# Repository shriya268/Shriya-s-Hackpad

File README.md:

# Shriya-s-Macropad
A macropad specifically designed for Roblox. The keys are necessary to play Roblox, and having only the necessary keys optimizes gaming performance. This is a macropad, not a HackPad, as I didn't use the tutorials for it and did it on my own. I made this project as a newcomer to PCB designing to learn. I've always found how daily systems such as keyboards work, but this is the first time I've made something like this myself.

# BOM

| Source     | Item                            | Quantity | Price  | Notes                                 | Link |
|------------|----------------------------------|----------|--------|----------------------------------------|------|
| AliExpress | M2 4mm Spacers                  | 5x       | $1.04  |                                        | [M2 4mm Spacers](https://www.aliexpress.us/item/3256807017784754.html?spm=a2g0o.productlist.0.0.722e6363EuH04s&mp=1&pdp_npi=5%40dis%21USD%21USD%201.48%21USD%201.04%21%21USD%201.04%21%21%21%402103277f17512608094343308ecd9e%2112000039794516573%21ct%21US%216408478558%21%211%210&_gl=1*11foqlg*_gcl_aw*R0NMLjE3NTExNDI5MTYuQ2owS0NRandwZjdDQmhDZkFSSXNBTklFVFZvTHNXX3MtcWgtVXdMc2JLR2MtUXRsWHN3RE9hdmVOSWRsZjQ3LWZ3UW1fUm92SXdEVWRtY2FBbm5ERUFMd193Y0I.*_gcl_au*MTQzODE4NjUwLjE3NTExNDI5MTY.*_ga*MTU5OTE5MTQzOC4xNzUxMjU5OTE5*_ga_VED1YSGNC7*czE3NTEyNTk5MTgkbzEkZzEkdDE3NTEyNjA4MTYkajMxJGwwJGgw&gatewayAdapt=glo2usa) |
| AliExpress | M2 7mm Spacers                  | 30x      | $2.10  |                                        | [M2 7mm Spacers](https://www.aliexpress.us/item/3256805863280885.html?spm=a2g0o.detail.0.0.1204wn00wn00uf&mp=1&pdp_npi=5%40dis%21USD%21USD%202.22%21USD%202.22%21%21USD%202.22%21%21%21%402103244817513077203134174eb19b%2112000035491390235%21ct%21US%216408478558%21%211%210&_gl=1*f6trlo*_gcl_aw*R0NMLjE3NTExNDI5MTYuQ2owS0NRandwZjdDQmhDZkFSSXNBTklFVFZvTHNXX3MtcWgtVXdMc2JLR2MtUXRsWHN3RE9hdmVOSWRsZjQ3LWZ3UW1fUm92SXdEVWRtY2FBbm5ERUFMd193Y0I.*_gcl_au*MTQzODE4NjUwLjE3NTExNDI5MTY.*_ga*MTU5OTE5MTQzOC4xNzUxMjU5OTE5*_ga_VED1YSGNC7*czE3NTEzMDc3MjAkbzIkZzAkdDE3NTEzMDc3MjAkajYwJGwwJGgw&gatewayAdapt=glo2usa) |
| AliExpress | M2 Screw Set                    | –        | $5.62  | Has all necessary lengths              | [M2 Screw Set](https://www.aliexpress.us/item/3256806973435795.html?spm=a2g0o.cart.0.0.56ac38daVxnwKY&mp=1&pdp_npi=5%40dis%21USD%21USD%205.88%21USD%205.62%21%21USD%205.62%21%21%21%402101ec1a17513583533687501ec24a%2112000039655872513%21ct%21US%216408478558%21%211%210&_gl=1*1bt5m9l*_gcl_aw*R0NMLjE3NTExNDI5MTYuQ2owS0NRandwZjdDQmhDZkFSSXNBTklFVFZvTHNXX3MtcWgtVXdMc2JLR2MtUXRsWHN3RE9hdmVOSWRsZjQ3LWZ3UW1fUm92SXdEVWRtY2FBbm5ERUFMd193Y0I.*_gcl_au*MTQzODE4NjUwLjE3NTExNDI5MTY.*_ga*MTU5OTE5MTQzOC4xNzUxMjU5OTE5*_ga_VED1YSGNC7*czE3NTEzNTc4ODYkbzQkZzEkdDE3NTEzNTgzNTQkajUyJGwwJGgw&gatewayAdapt=glo2usa)|
| AliExpress | DO-35 Diodes                    | 100x     | $0.99  |                                        | [DO-35 Diodes](https://www.aliexpress.com/item/2251832667767786.html?spm=a2g0o.cart.0.0.798a38daLnZwjx&mp=1&pdp_npi=5%40dis%21USD%21USD%203.51%21USD%203.51%21%21USD%203.51%21%21%21%40210337bc17513078928717653e059c%2167121545639%21ct%21US%216408478558%21%211%210&_gl=1*huzjkp*_gcl_aw*R0NMLjE3NTExNDI5MTYuQ2owS0NRandwZjdDQmhDZkFSSXNBTklFVFZvTHNXX3MtcWgtVXdMc2JLR2MtUXRsWHN3RE9hdmVOSWRsZjQ3LWZ3UW1fUm92SXdEVWRtY2FBbm5ERUFMd193Y0I.*_gcl_au*MTQzODE4NjUwLjE3NTExNDI5MTY.*_ga*MTU5OTE5MTQzOC4xNzUxMjU5OTE5*_ga_VED1YSGNC7*czE3NTEzMDc3MjAkbzIkZzEkdDE3NTEzMDc5MTQkajMkbDAkaDA) |
| AliExpress | Cherry MX Keycaps               | 104x     | $5.01  |                                        | [Cherry MX Keycaps](https://www.aliexpress.us/item/3256808108935624.html?spm=a2g0o.cart.0.0.3f1638daol5bNF&mp=1&pdp_npi=5%40dis%21USD%21USD%205.01%21USD%205.01%21%21USD%205.01%21%21%21%40210318c317513586402145101e623c%2112000044523183107%21ct%21US%216408478558%21%211%210&_gl=1*bvs7nr*_gcl_aw*R0NMLjE3NTExNDI5MTYuQ2owS0NRandwZjdDQmhDZkFSSXNBTklFVFZvTHNXX3MtcWgtVXdMc2JLR2MtUXRsWHN3RE9hdmVOSWRsZjQ3LWZ3UW1fUm92SXdEVWRtY2FBbm5ERUFMd193Y0I.*_gcl_au*MTQzODE4NjUwLjE3NTExNDI5MTY.*_ga*MTU5OTE5MTQzOC4xNzUxMjU5OTE5*_ga_VED1YSGNC7*czE3NTEzNTc4ODYkbzQkZzEkdDE3NTEzNTg2MzQkajU2JGwwJGgw&gatewayAdapt=glo2usa) |
| Amazon     | Cherry MX Red Keyswitches       | 23x      | $9.60  | 20% off discount + Amazon Prime        | [Cherry MX Red Keyswitches](https://www.amazon.com/gp/product/B0CBS4HJJR/ref=ox_sc_saved_image_1?smid=AK7PAPV76H5NA&th=1) |
| Keebio     | Arduino Pro Micro               | 1x       | $7.99  | 5V 16MHz ATmega32U4                    | [Arduino Pro Micro](https://keeb.io/products/pro-micro-5v-16mhz-arduino-compatible-atmega32u4?srsltid=AfmBOoohKZiYkrMl3YAv38JQXlnb-arPQS6xtnZeeLZ4_bFDnoDUEZKH) |
| JLCPCB     | Custom PCBs                     | 5x       | $5.30  |                                        | [JLCPCB Cart](https://cart.jlcpcb.com/shopcart/cart/) |
| **Total**  |                                  |          | **$37.65** |                                      |      |

*AliExpress products are so cheap because of the welcome deal and additional coupons/discounts

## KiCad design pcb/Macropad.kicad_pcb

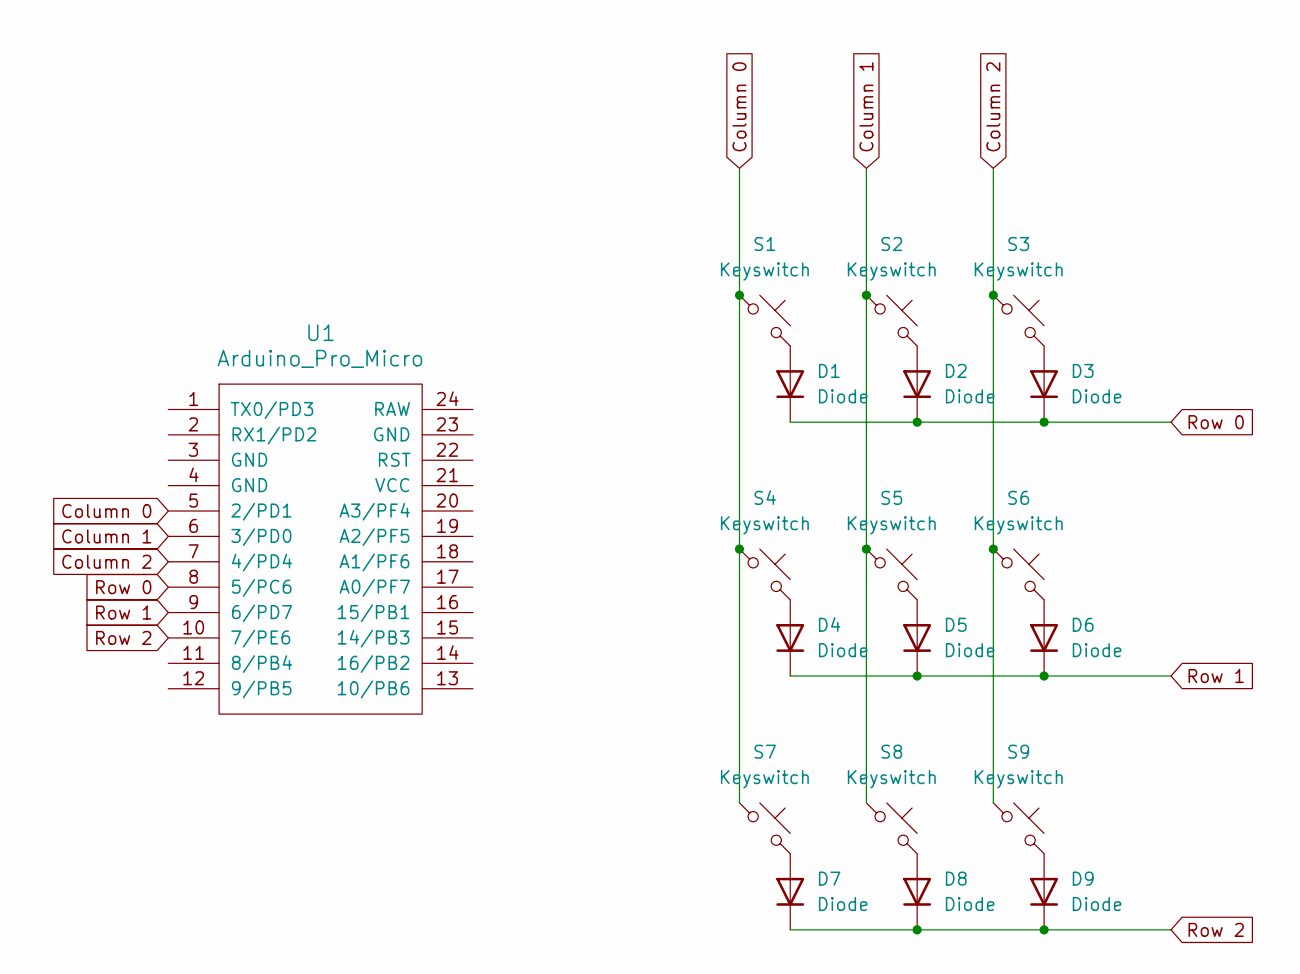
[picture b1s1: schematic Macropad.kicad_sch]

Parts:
D1, D2, D3, D4, D5, D6, D7, D8, D9: Diode; Diode_DO-35
S1, S2, S3, S4, S5, S6, S7, S8, S9: Keyswitch; MX_PCB_1.00u
U1: Arduino_Pro_Micro

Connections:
Column 0: S1.1, S4.1, S7.1, U1.5 (2/PD1)
Column 1: S2.1, S5.1, S8.1, U1.6 (3/PD0)
Column 2: S3.1, S6.1, S9.1, U1.7 (4/PD4)
unnamed: D1.2 (A), S1.2
unnamed: D2.2 (A), S2.2
unnamed: D3.2 (A), S3.2
unnamed: D4.2 (A), S4.2
unnamed: D5.2 (A), S5.2
unnamed: D6.2 (A), S6.2
unnamed: D7.2 (A), S7.2
unnamed: D8.2 (A), S8.2
unnamed: D9.2 (A), S9.2
Row 0: D1.1 (K), D2.1 (K), D3.1 (K), U1.8 (5/PC6)
Row 1: D4.1 (K), D5.1 (K), D6.1 (K), U1.9 (6/PD7)
Row 2: D7.1 (K), D8.1 (K), D9.1 (K), U1.10 (7/PE6)

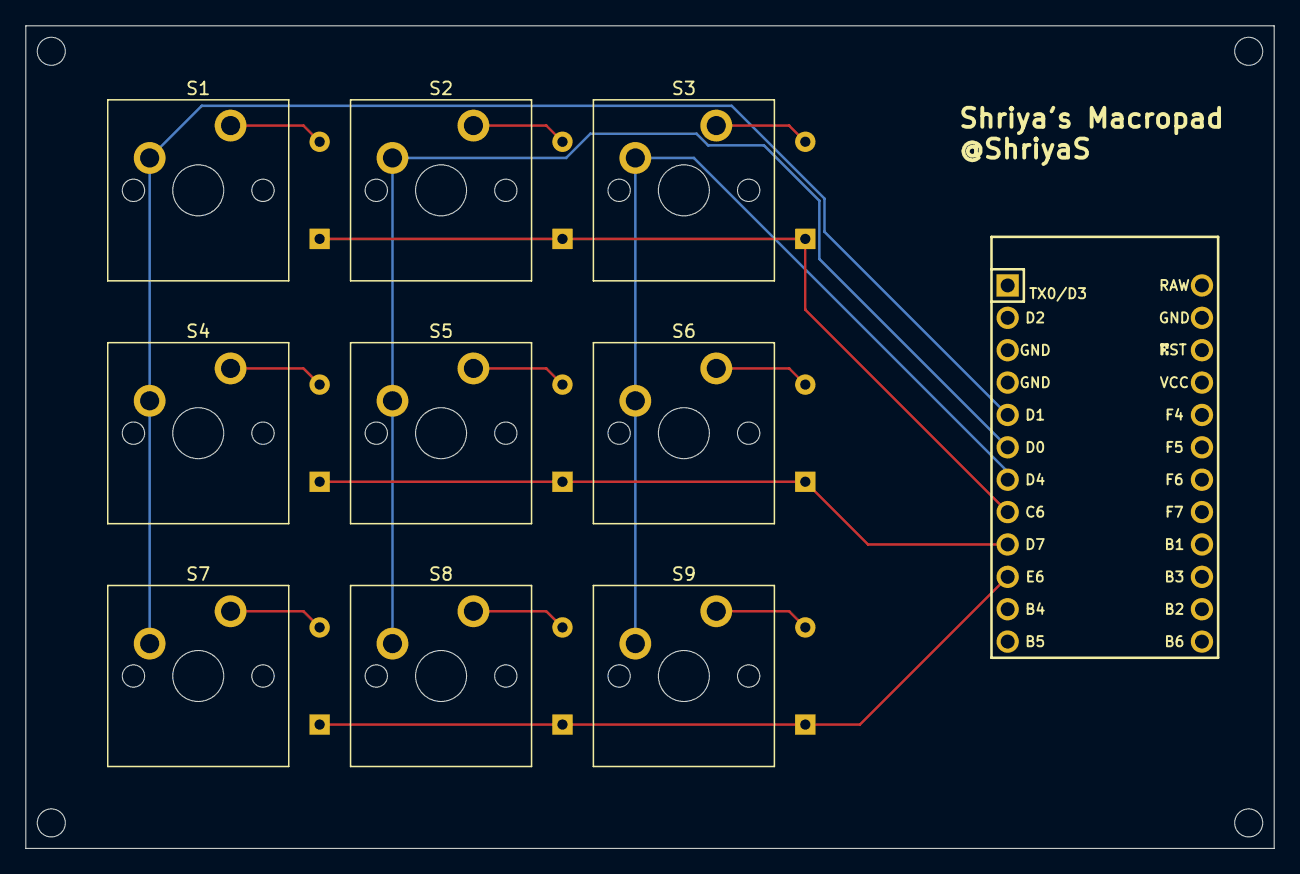
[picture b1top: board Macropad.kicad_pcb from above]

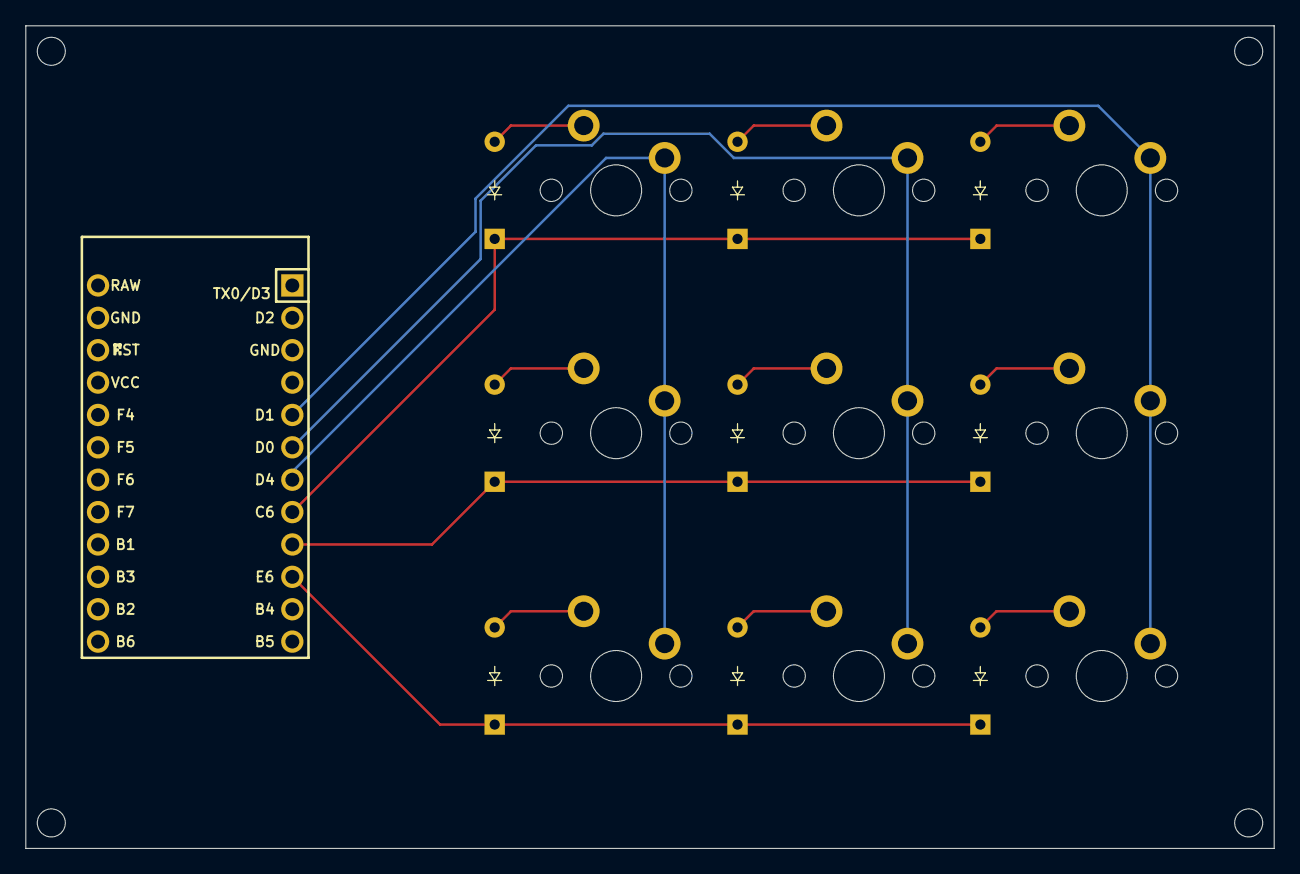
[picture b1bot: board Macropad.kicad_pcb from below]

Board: 2 copper layers, 97.9 x 64.5 mm, 19 parts (9 on the bottom side), 15 nets.

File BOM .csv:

Designator,Footprint,Quantity,Value
"D1, D2, D3, D4, D5, D6, D7, D8, D9",Diode_DO-35,9,1N4148
"S1, S2, S3, S4, S5, S6, S7, S8, S9",MX_PCB_1.00u,9,Cherry MX
U1,Arduino_Pro_Micro,1,ATmega32U3

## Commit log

2025-06-29 README.md
2025-06-29 firmware.py
2025-06-29 bom.csv
2025-06-29 cad 1
2025-06-29 Journal.md
